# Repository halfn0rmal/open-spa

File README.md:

# open-spa
Open source spa pool controller

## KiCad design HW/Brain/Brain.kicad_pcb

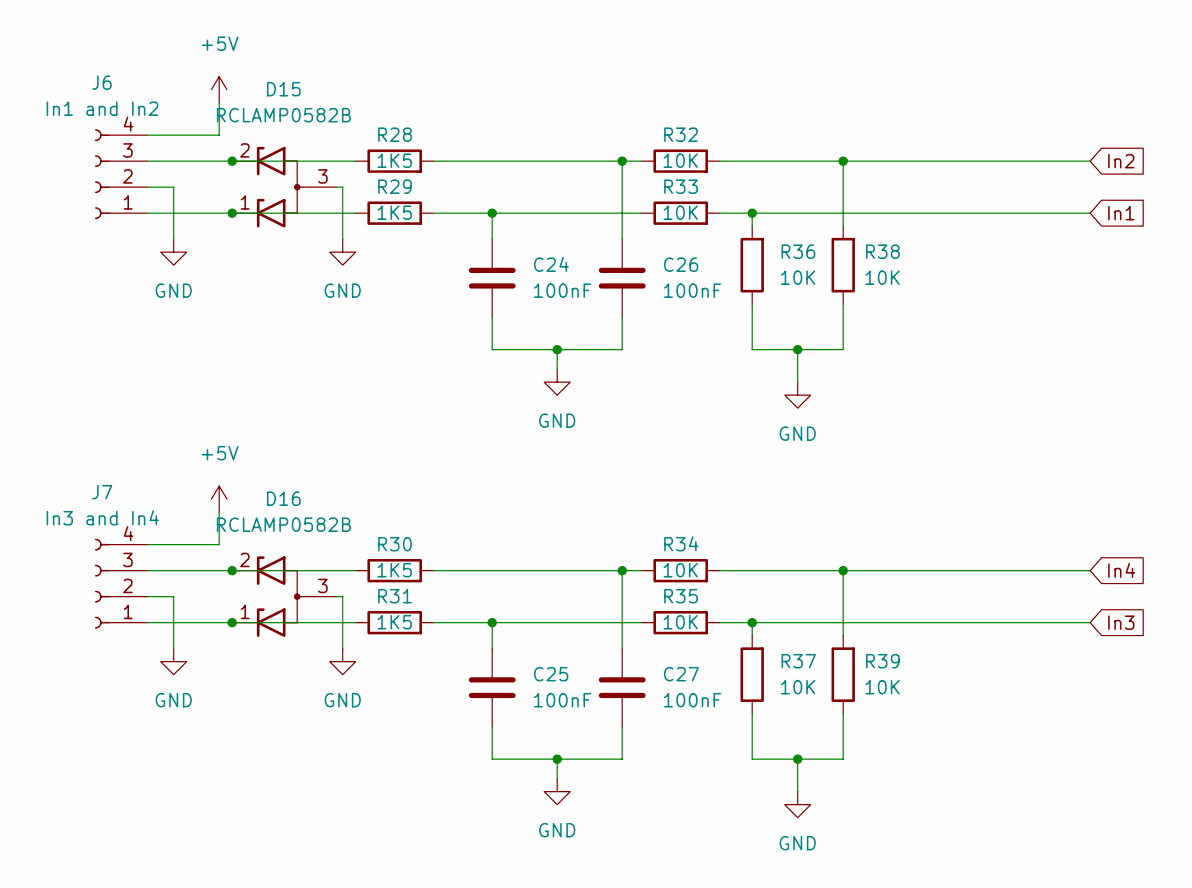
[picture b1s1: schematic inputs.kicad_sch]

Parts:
C24, C25, C26, C27: 100nF; C_0603_1608Metric_Pad1.08x0.95mm_HandSolder
D15, D16: RCLAMP0582B; SOT-416
J6: In1 and In2; PhoenixContact_MSTBVA_2,5_4-G_1x04_P5.00mm_Vertical
J7: In3 and In4; PhoenixContact_MSTBVA_2,5_4-G_1x04_P5.00mm_Vertical
R28, R29, R30, R31: 1K5; R_0603_1608Metric_Pad0.98x0.95mm_HandSolder
R32, R33, R34, R35, R36, R37, R38, R39: 10K; R_0603_1608Metric_Pad0.98x0.95mm_HandSolder

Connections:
+5V: J6.4, J7.4; also elsewhere on the board
GND: C24.2, C25.2, C26.2, C27.2, D15.3 (A), D16.3 (A), J6.2, J7.2, R36.1, R37.1, R38.1, R39.1; also elsewhere on the board
In1: R33.2, R36.2; also elsewhere on the board
In2: R32.2, R38.2; also elsewhere on the board
In3: R35.2, R37.2; also elsewhere on the board
In4: R34.2, R39.2; also elsewhere on the board
unnamed: C24.1, R29.2, R33.1
unnamed: C25.1, R31.2, R35.1
unnamed: C26.1, R28.2, R32.1
unnamed: C27.1, R30.2, R34.1
unnamed: D15.1 (K1), J6.1, R29.1
unnamed: D15.2 (K2), J6.3, R28.1
unnamed: D16.1 (K1), J7.1, R31.1
unnamed: D16.2 (K2), J7.3, R30.1

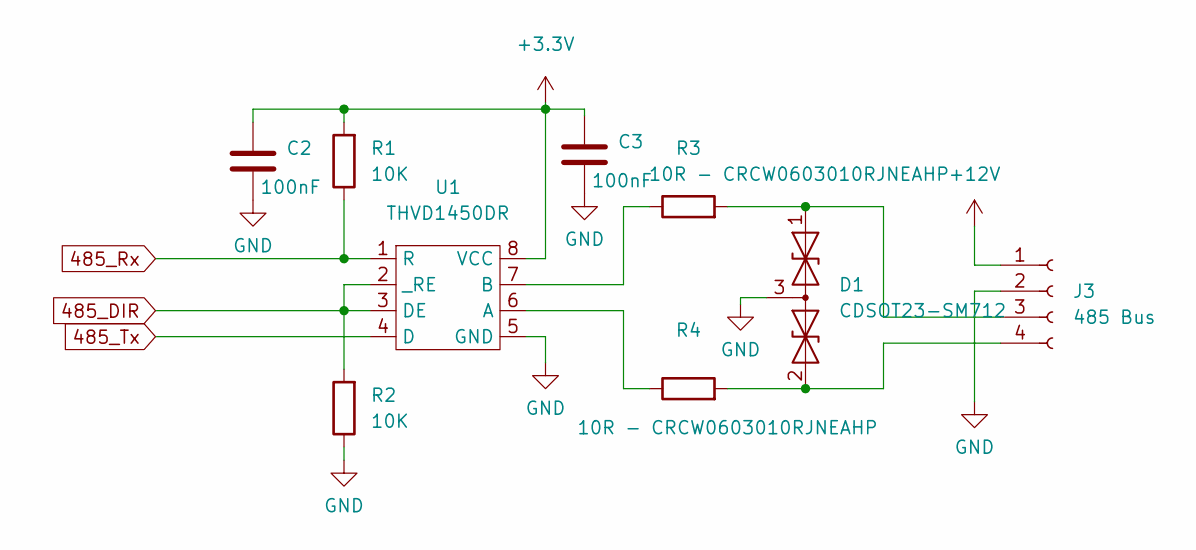
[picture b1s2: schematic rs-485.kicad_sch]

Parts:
C2, C3: 100nF; C_0603_1608Metric
D1: CDSOT23-SM712; SOT-23
J3: 485 Bus; PhoenixContact_MSTBVA_2,5_4-G_1x04_P5.00mm_Vertical
R1, R2: 10K; R_0603_1608Metric_Pad0.98x0.95mm_HandSolder
R3, R4: 10R - CRCW0603010RJNEAHP; R_0603_1608Metric_Pad0.98x0.95mm_HandSolder
U1: THVD1450DR; SOIC-8_3.9x4.9mm_P1.27mm

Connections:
485_DIR: R2.2, U1.2 (_RE), U1.3 (DE); also elsewhere on the board
485_Rx: R1.1, U1.1 (R); also elsewhere on the board
485_Tx: U1.4 (D); also elsewhere on the board
+3.3V: C2.1, C3.1, R1.2, U1.8 (VCC); also elsewhere on the board
+12V: J3.1; also elsewhere on the board
GND: C2.2, C3.2, D1.3 (common), J3.2, R2.1, U1.5 (GND); also elsewhere on the board
unnamed: D1.1 (A1), J3.3, R3.2
unnamed: D1.2 (A2), J3.4, R4.2
unnamed: R3.1, U1.7 (B)
unnamed: R4.1, U1.6 (A)

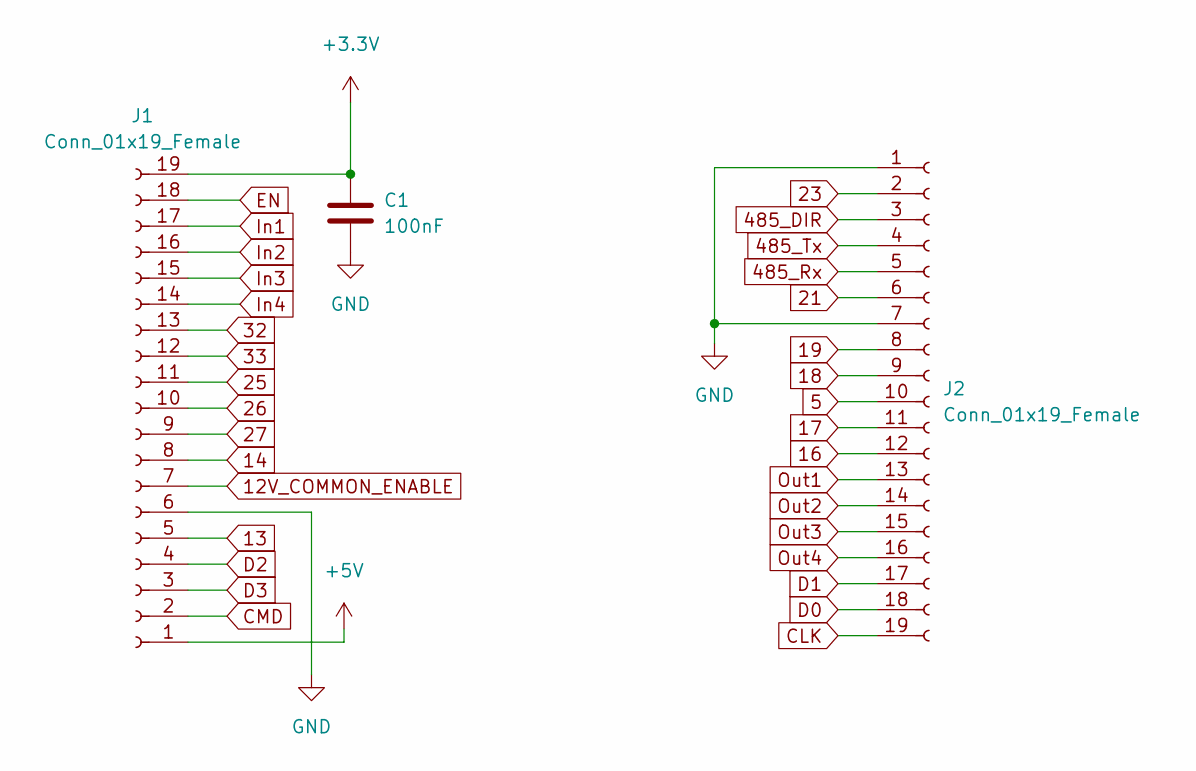
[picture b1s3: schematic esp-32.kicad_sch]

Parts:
C1: 100nF; C_0603_1608Metric
J1, J2: Conn_01x19_Female; PinSocket_1x19_P2.54mm_Vertical

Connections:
5: J2.10
12V_COMMON_ENABLE: J1.7; also elsewhere on the board
13: J1.5
14: J1.8
16: J2.12
17: J2.11
18: J2.9
19: J2.8
21: J2.6
23: J2.2
25: J1.11
26: J1.10
27: J1.9
32: J1.13
33: J1.12
485_DIR: J2.3; also elsewhere on the board
485_Rx: J2.5; also elsewhere on the board
485_Tx: J2.4; also elsewhere on the board
+3.3V: C1.1, J1.19; also elsewhere on the board
+5V: J1.1; also elsewhere on the board
CLK: J2.19
CMD: J1.2
D0: J2.18
D1: J2.17
D2: J1.4
D3: J1.3
EN: J1.18
GND: C1.2, J1.6, J2.1, J2.7; also elsewhere on the board
In1: J1.17; also elsewhere on the board
In2: J1.16; also elsewhere on the board
In3: J1.15; also elsewhere on the board
In4: J1.14; also elsewhere on the board
Out1: J2.13; also elsewhere on the board
Out2: J2.14; also elsewhere on the board
Out3: J2.15; also elsewhere on the board
Out4: J2.16; also elsewhere on the board

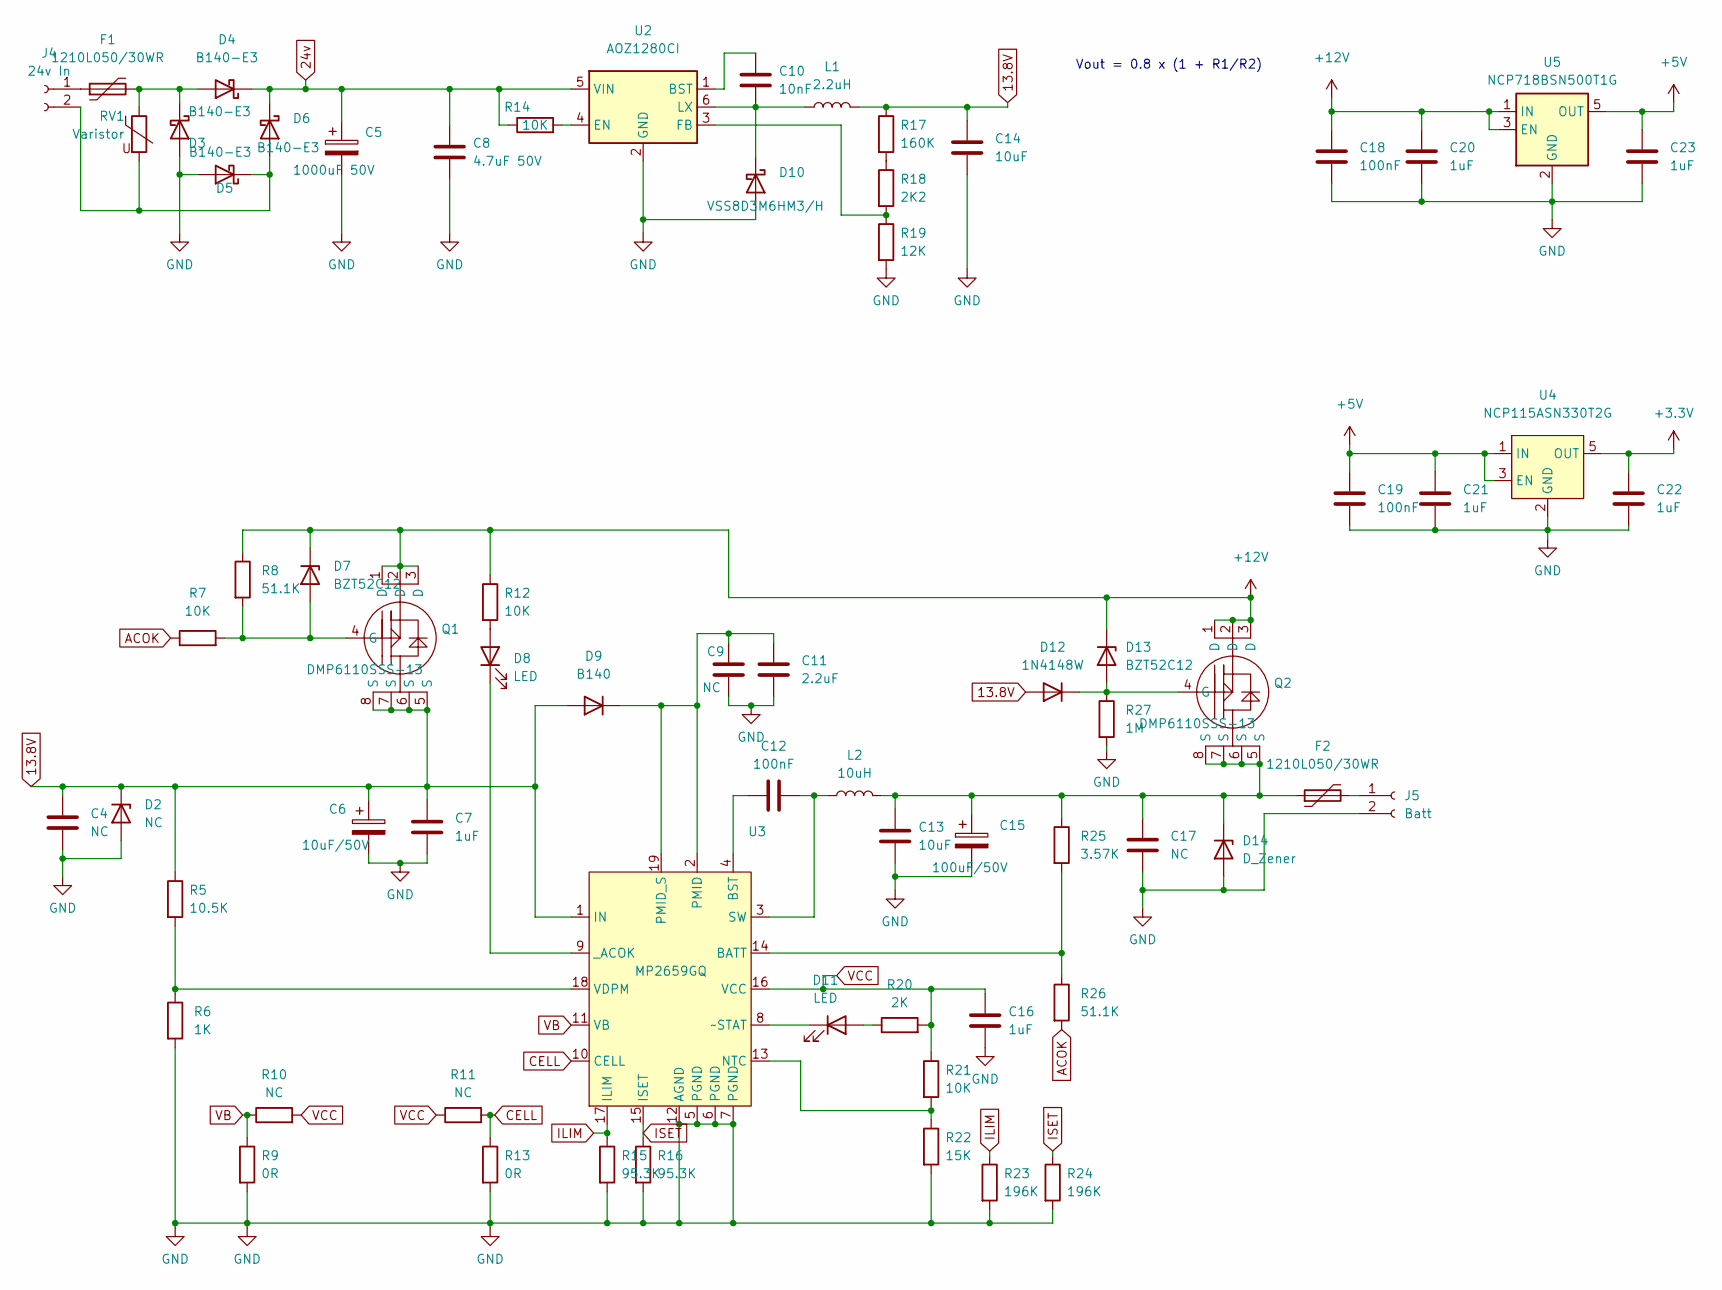
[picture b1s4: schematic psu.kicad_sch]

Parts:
C4, C9, C17: NC; C_0603_1608Metric
C5: 1000uF 50V; CP_Radial_D12.5mm_P5.00mm
C6: 10uF/50V; CP_Elec_3x5.3
C7, C16: 1uF; C_0603_1608Metric
C8: 4.7uF 50V; C_0805_2012Metric
C10: 10nF; C_0603_1608Metric
C11: 2.2uF; C_0603_1608Metric
C12: 100nF; C_0603_1608Metric
C13, C14: 10uF; C_0603_1608Metric
C15: 100uF/50V; CP_Elec_8x6.9
C18, C19: 100nF; C_0603_1608Metric_Pad1.08x0.95mm_HandSolder
C20, C21, C22, C23: 1uF; C_0603_1608Metric_Pad1.08x0.95mm_HandSolder
D2: NC; SOT-23
D3, D4, D5, D6: B140-E3; D_SMA
D7, D13: BZT52C12; D_SOD-123
D8, D11: LED; LED_0603_1608Metric_Pad1.05x0.95mm_HandSolder
D9: B140; D_SOD-123
D10: VSS8D3M6HM3/H; DO-221AD
D12: 1N4148W; D_SOD-123
D14: D_Zener; D_SOD-123
F1, F2: 1210L050/30WR; Fuse_1210_3225Metric
J4: 24v In; PhoenixContact_MSTBVA_2,5_2-G_1x02_P5.00mm_Vertical
J5: Batt; PhoenixContact_MSTBVA_2,5_2-G_1x02_P5.00mm_Vertical
L1: 2.2uH; LQH32PH2R2NNCL
L2: 10uH; CDRH8D43NP-100NC
Q1, Q2: DMP6110SSS-13; SO-8_3.9x4.9mm_P1.27mm
R5: 10.5K; R_0603_1608Metric_Pad0.98x0.95mm_HandSolder
R6: 1K; R_0603_1608Metric_Pad0.98x0.95mm_HandSolder
R7, R12, R14, R21: 10K; R_0603_1608Metric_Pad0.98x0.95mm_HandSolder
R8, R26: 51.1K; R_0603_1608Metric_Pad0.98x0.95mm_HandSolder
R9, R13: 0R; R_0603_1608Metric_Pad0.98x0.95mm_HandSolder
R10, R11: NC; R_0603_1608Metric_Pad0.98x0.95mm_HandSolder
R15, R16: 95.3K; R_0603_1608Metric_Pad0.98x0.95mm_HandSolder
R17: 160K; R_0603_1608Metric_Pad0.98x0.95mm_HandSolder
R18: 2K2; R_0603_1608Metric_Pad0.98x0.95mm_HandSolder
R19: 12K; R_0603_1608Metric_Pad0.98x0.95mm_HandSolder
R20: 2K; R_0603_1608Metric_Pad0.98x0.95mm_HandSolder
R22: 15K; R_0603_1608Metric_Pad0.98x0.95mm_HandSolder
R23, R24: 196K; R_0603_1608Metric_Pad0.98x0.95mm_HandSolder
R25: 3.57K; R_0603_1608Metric_Pad0.98x0.95mm_HandSolder
R27: 1M; R_0603_1608Metric_Pad0.98x0.95mm_HandSolder
RV1: Varistor; R_1206_3216Metric_Pad1.30x1.75mm_HandSolder
U2: AOZ1280CI; SOT-23-6
U3: MP2659GQ; QFN-19_MP2659_MNP
U4: NCP115ASN330T2G; TSOP-5_1.65x3.05mm_P0.95mm
U5: NCP718BSN500T1G; SOT-23-5

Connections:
13.8V: C4.2, C6.1, C7.2, C14.1, D2.1 (K), D9.2 (A), D12.2 (A), L1.2, Q1.5 (S), Q1.6 (S), Q1.7 (S), Q1.8 (S), R5.1, R17.1, U3.1 (IN)
24v: C5.1, C8.1, D4.1 (K), D6.1 (K), R14.1, U2.5 (VIN)
+3.3V: C22.1, U4.5 (OUT); also elsewhere on the board
+5V: C19.1, C21.1, C23.1, U4.1 (IN), U4.3 (EN), U5.5 (OUT); also elsewhere on the board
+12V: C18.1, C20.1, D7.1 (K), D13.1 (K), Q1.1 (D), Q1.2 (D), Q1.3 (D), Q2.1 (D), Q2.2 (D), Q2.3 (D), R8.1, R12.1, U5.1 (IN), U5.3 (EN); also elsewhere on the board
ACOK: R7.1, R26.2
CELL: R11.2, R13.1, U3.10 (CELL)
GND: C4.1, C5.2, C6.2, C7.1, C8.2, C9.1, C11.1, C13.1, C14.2, C15.2, C16.1, C17.1, C18.2, C19.2, C20.2, C21.2, C22.2, C23.2, D2.2 (A), D3.2 (A), D5.2 (A), D10.2 (A), D14.2 (A), J5.2, R6.2, R9.2, R13.2, R15.2, R16.2, R19.2, R22.2, R23.2, R24.2, R27.2, U2.2 (GND), U3.5 (PGND), U3.6 (PGND), U3.7 (PGND), U3.12 (AGND), U4.2 (GND), U5.2 (GND); also elsewhere on the board
ILIM: R15.1, R23.1, U3.17 (ILIM)
ISET: R16.1, R24.1, U3.15 (ISET)
unnamed: C10.1, U2.1 (BST)
unnamed: C10.2, D10.1 (K), L1.1, U2.6 (LX)
unnamed: C9.2, C11.2, D9.1 (K), U3.2 (PMID), U3.19 (PMID_S)
unnamed: C12.1, U3.4 (BST)
unnamed: C12.2, L2.1, U3.3 (SW)
unnamed: C13.2, C15.1, C17.2, D14.1 (K), F2.1, L2.2, Q2.5 (S), Q2.6 (S), Q2.7 (S), Q2.8 (S), R25.1
unnamed: D3.1 (K), D4.2 (A), F1.2, RV1.1
unnamed: D5.1 (K), D6.2 (A), J4.2, RV1.2
unnamed: D7.2 (A), Q1.4 (G), R7.2, R8.2
unnamed: D8.1 (K), U3.9 (_ACOK)
unnamed: D8.2 (A), R12.2
unnamed: D11.1 (K), U3.8 (~STAT)
unnamed: D11.2 (A), R20.1
unnamed: D12.1 (K), D13.2 (A), Q2.4 (G), R27.1
unnamed: F1.1, J4.1
unnamed: F2.2, J5.1
unnamed: R5.2, R6.1, U3.18 (VDPM)
unnamed: R14.2, U2.4 (EN)
unnamed: R17.2, R18.1
unnamed: R18.2, R19.1, U2.3 (FB)
unnamed: R21.2, R22.1, U3.13 (NTC)
unnamed: R25.2, R26.1, U3.14 (BATT)
VB: R9.1, R10.1, U3.11 (VB)
VCC: C16.2, R10.2, R11.1, R20.2, R21.1, U3.16 (VCC)

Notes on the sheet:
Vout = 0.8 x (1 + R1/R2)

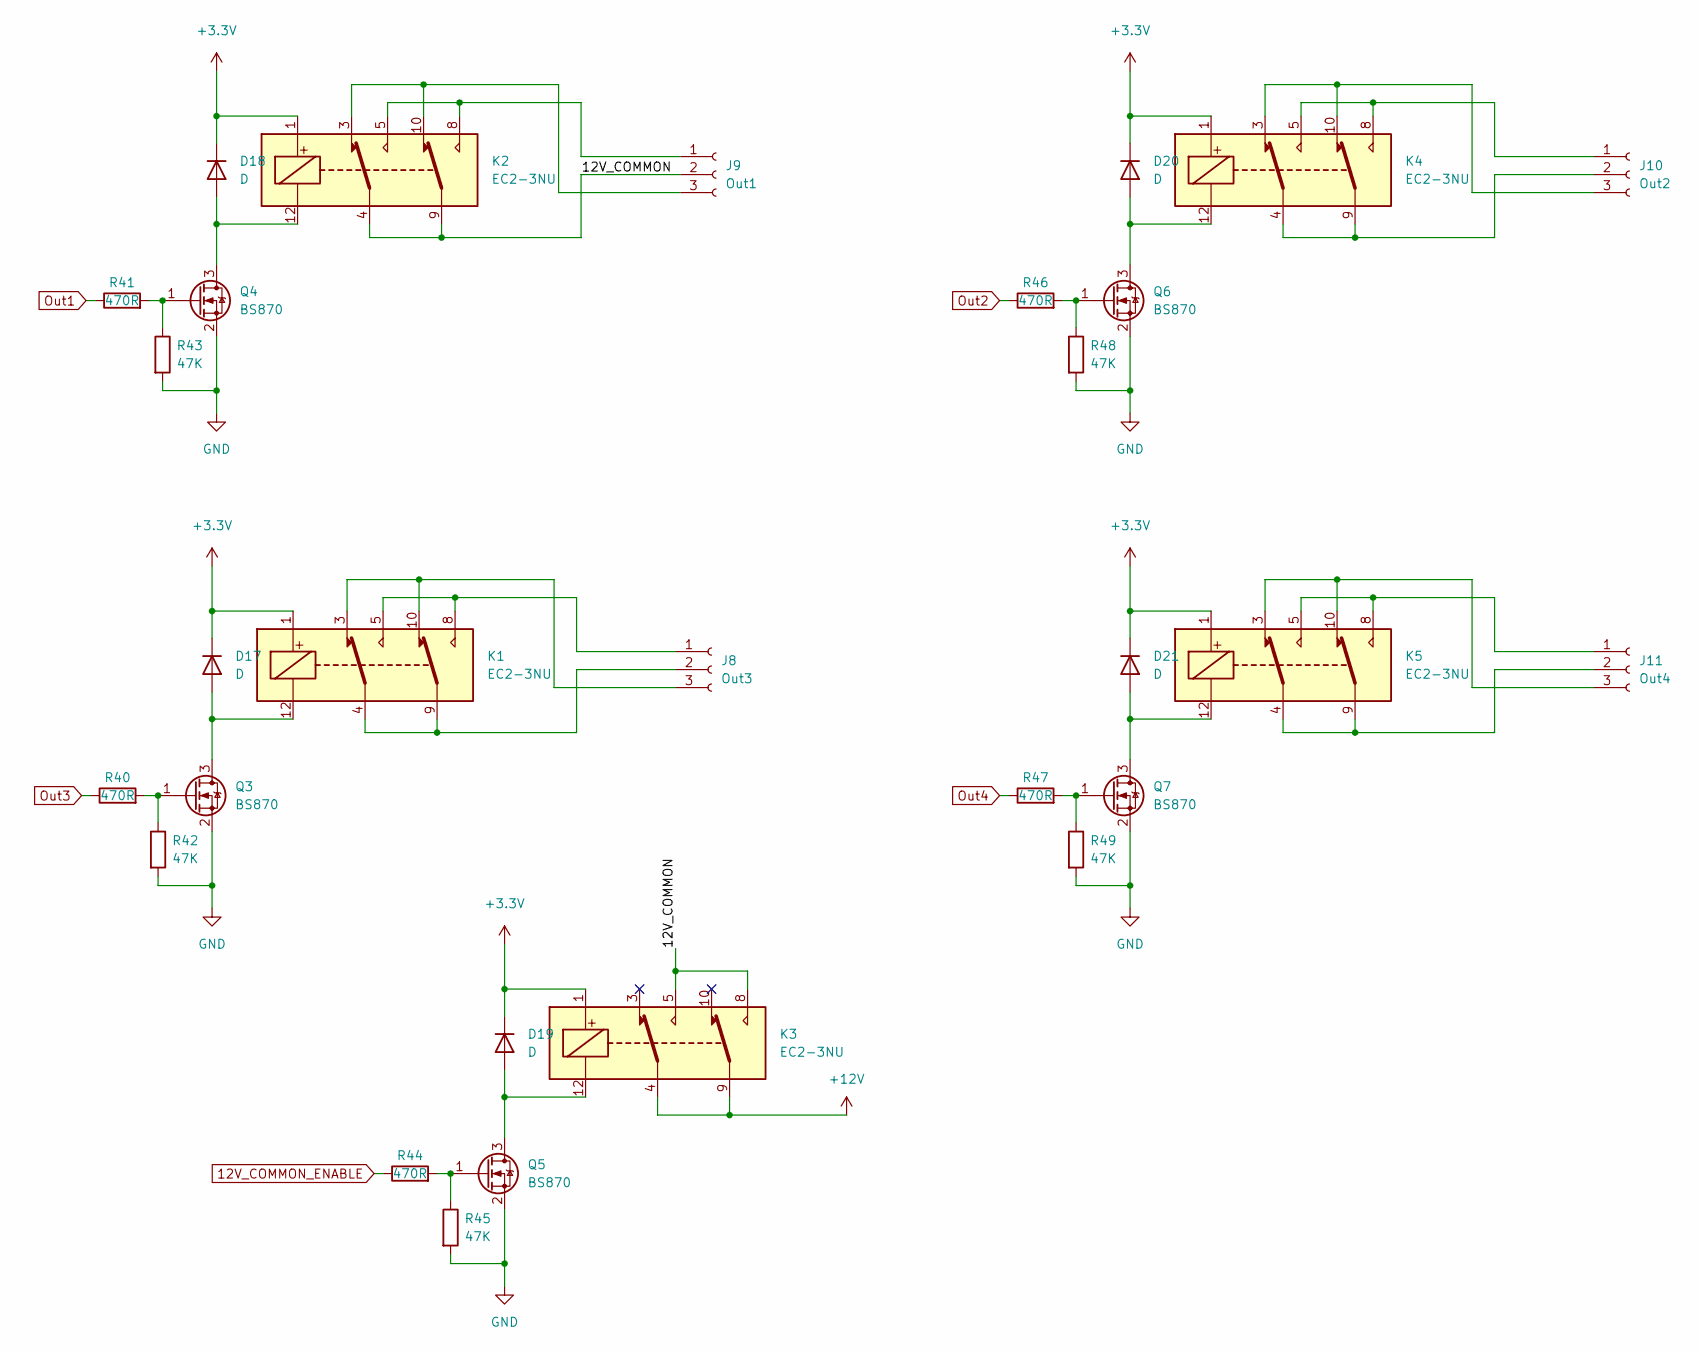
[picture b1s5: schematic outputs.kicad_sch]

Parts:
D17, D18, D19, D20, D21: D; D_SOD-123
J8: Out3; PhoenixContact_MSTBVA_2,5_3-G_1x03_P5.00mm_Vertical
J9: Out1; PhoenixContact_MSTBVA_2,5_3-G_1x03_P5.00mm_Vertical
J10: Out2; PhoenixContact_MSTBVA_2,5_3-G_1x03_P5.00mm_Vertical
J11: Out4; PhoenixContact_MSTBVA_2,5_3-G_1x03_P5.00mm_Vertical
K1, K2, K3, K4, K5: EC2-3NU; Relay_DPDT_Kemet_EC2
Q3, Q4, Q5, Q6, Q7: BS870; SOT-23
R40, R41, R44, R46, R47: 470R; R_0603_1608Metric_Pad0.98x0.95mm_HandSolder
R42, R43, R45, R48, R49: 47K; R_0603_1608Metric_Pad0.98x0.95mm_HandSolder

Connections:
12V_COMMON_ENABLE: R44.1; also elsewhere on the board
+3.3V: D17.1 (K), D18.1 (K), D19.1 (K), D20.1 (K), D21.1 (K), K1.1, K2.1, K3.1, K4.1, K5.1; also elsewhere on the board
+12V: K3.4, K3.9; also elsewhere on the board
/Outputs/12V_COMMON: J9.2, K2.4, K2.9, K3.5, K3.8
GND: Q3.2 (S), Q4.2 (S), Q5.2 (S), Q6.2 (S), Q7.2 (S), R42.2, R43.2, R45.2, R48.2, R49.2; also elsewhere on the board
unnamed: D17.2 (A), K1.12, Q3.3 (D)
unnamed: D18.2 (A), K2.12, Q4.3 (D)
unnamed: D19.2 (A), K3.12, Q5.3 (D)
unnamed: D20.2 (A), K4.12, Q6.3 (D)
unnamed: D21.2 (A), K5.12, Q7.3 (D)
unnamed: J8.1, K1.5, K1.8
unnamed: J8.2, K1.4, K1.9
unnamed: J8.3, K1.3, K1.10
unnamed: J9.1, K2.5, K2.8
unnamed: J9.3, K2.3, K2.10
unnamed: J10.1, K4.5, K4.8
unnamed: J10.2, K4.4, K4.9
unnamed: J10.3, K4.3, K4.10
unnamed: J11.1, K5.5, K5.8
unnamed: J11.2, K5.4, K5.9
unnamed: J11.3, K5.3, K5.10
unnamed: Q3.1 (G), R40.2, R42.1
unnamed: Q4.1 (G), R41.2, R43.1
unnamed: Q5.1 (G), R44.2, R45.1
unnamed: Q6.1 (G), R46.2, R48.1
unnamed: Q7.1 (G), R47.2, R49.1
Out1: R41.1; also elsewhere on the board
Out2: R46.1; also elsewhere on the board
Out3: R40.1; also elsewhere on the board
Out4: R47.1; also elsewhere on the board

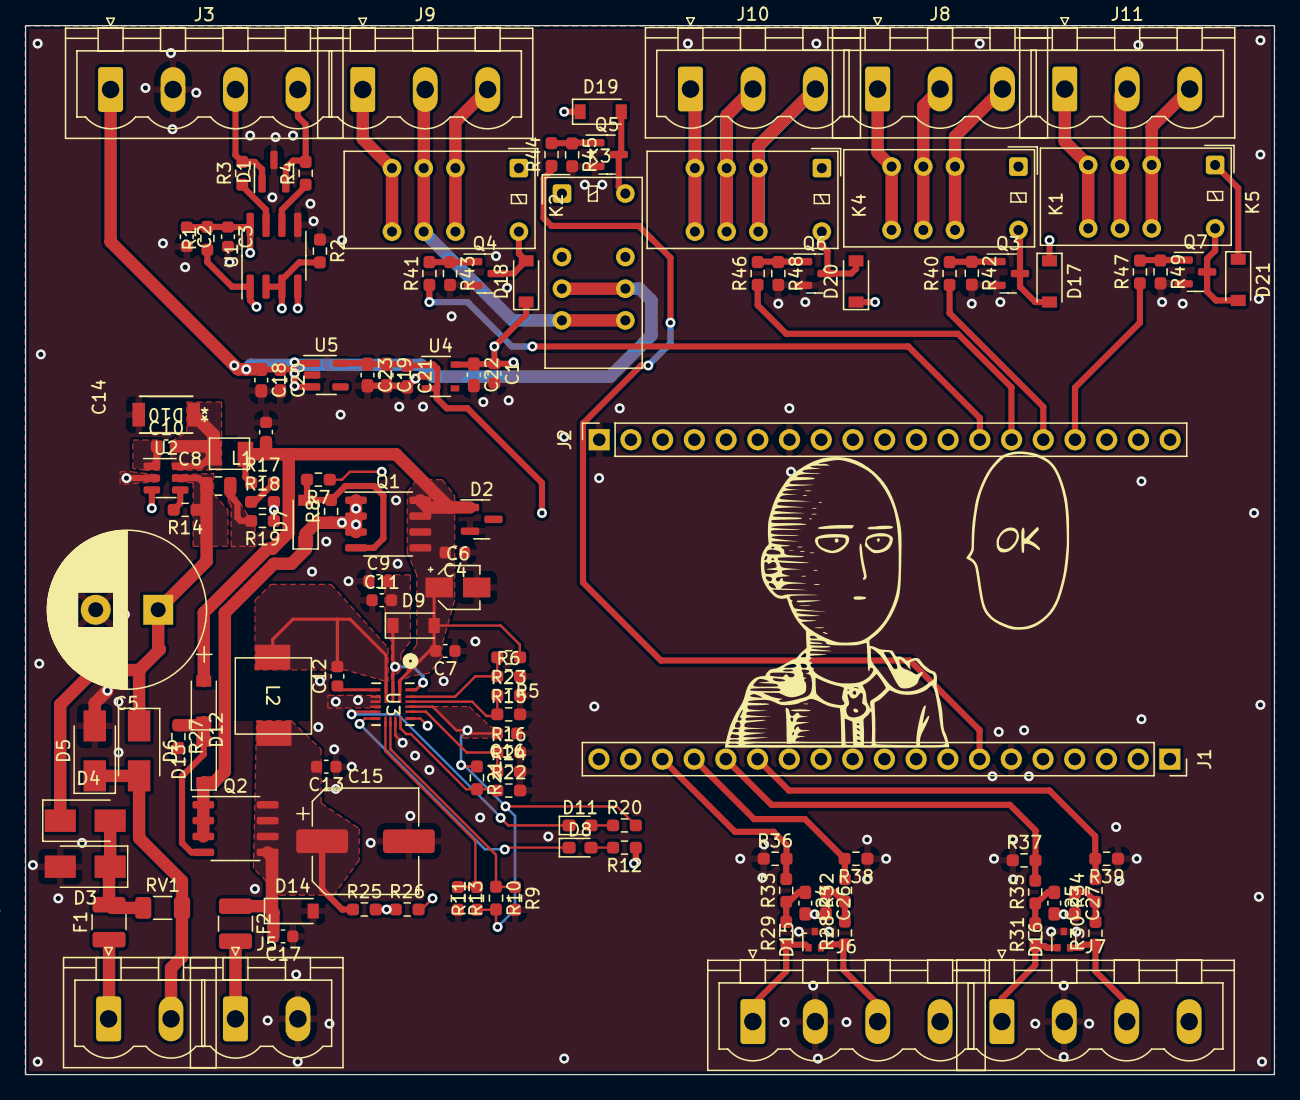
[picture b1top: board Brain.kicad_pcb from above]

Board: 4 copper layers, 100.0 x 84.0 mm, 130 parts (0 on the bottom side), 80 nets.

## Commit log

2023-12-12 Add HW v1
2024-03-07 First version
2024-03-17 firmware
